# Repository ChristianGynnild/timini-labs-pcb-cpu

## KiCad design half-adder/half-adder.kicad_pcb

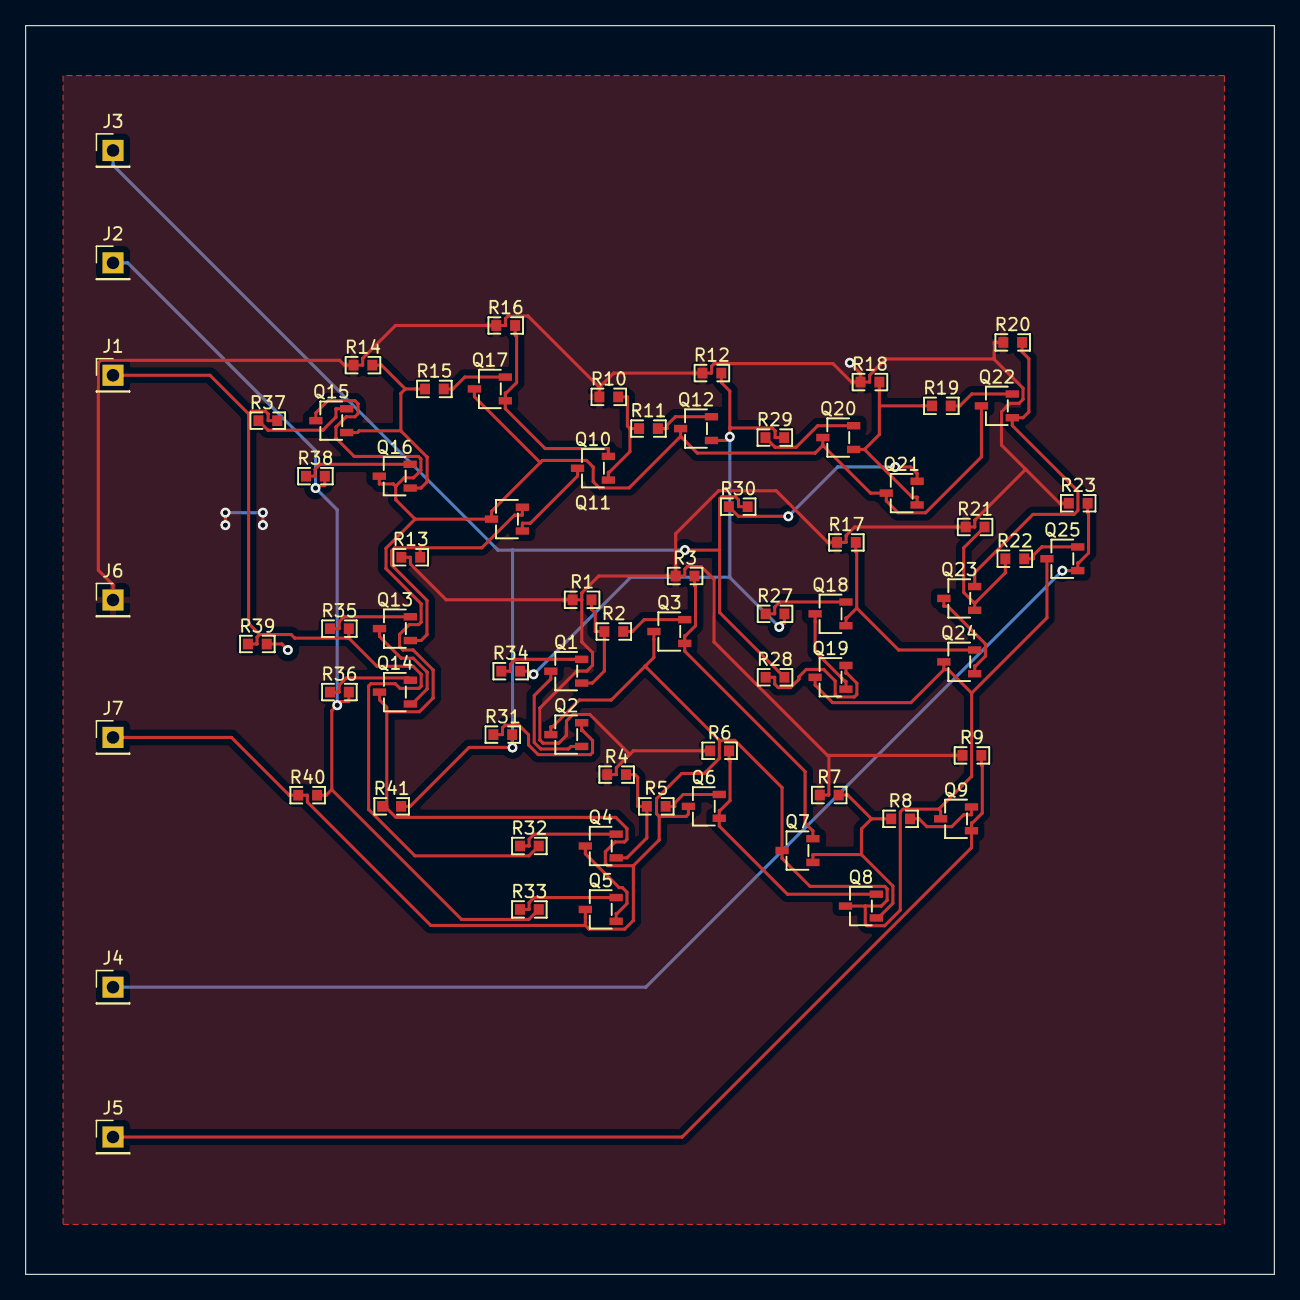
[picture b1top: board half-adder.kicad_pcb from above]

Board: 2 copper layers, 100.0 x 100.0 mm, 70 parts (0 on the bottom side), 46 nets.

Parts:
J1: A; PinHeader_1x01_P2.54mm_Vertical
J2: B; PinHeader_1x01_P2.54mm_Vertical
J3: C; PinHeader_1x01_P2.54mm_Vertical
J4: OUTPUT; PinHeader_1x01_P2.54mm_Vertical
J5: CARRY OUT; PinHeader_1x01_P2.54mm_Vertical
J6: 5V; PinHeader_1x01_P2.54mm_Vertical
J7: GROUND; PinHeader_1x01_P2.54mm_Vertical
Q1, Q2, Q3, Q4, Q5, Q6, Q7, Q8, Q9, Q10, Q11, Q12, Q13, Q14, Q15, Q16, Q17, Q18, Q19, Q20, Q21, Q22, Q23, Q24, Q25: NPN; SOT-23-3_L2.9-W1.6-P1.90-LS2.8-BR
R1, R3, R7, R8, R9, R10, R11, R12, R13, R14, R15, R16, R17, R18, R19, R20, R21, R22, R23: 3k; R0603
R2, R4, R5, R6: 1k; R0603
R27, R28, R29, R30, R31, R32, R33, R34, R35, R36, R37, R38: 10k; R0603
R39, R40, R41: 50k; R0603

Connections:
+5V: J6.1, R1.1, R3.1, R4.1, R6.1, R7.1, R9.1, R10.1, R12.1, R13.1, R14.1, R16.1, R17.1, R18.1, R20.1, R21.1, R23.1
/ORa: Q3.1 (C), Q7.2 (B), R3.2
/ORb: Q6.1 (C), Q8.2 (B), R6.2
GND: J7.1, Q2.3 (E), Q3.3 (E), Q5.3 (E), Q6.3 (E), Q7.3 (E), Q8.3 (E), Q9.3 (E), Q11.3 (E), Q12.3 (E), Q14.3 (E), Q15.3 (E), Q16.3 (E), Q17.3 (E), Q19.3 (E), Q20.3 (E), Q21.3 (E), Q22.3 (E), Q24.3 (E), Q25.3 (E), R39.2, R40.1, R41.1
unnamed: J1.1, R32.2, R35.2, R37.2, R39.1
unnamed: J2.1, R33.2, R36.2, R38.2, R40.2
unnamed: J3.1, R28.2, R30.2, R31.2, R41.2
unnamed: J4.1, Q25.1 (C), R23.2
unnamed: J5.1, Q9.1 (C), R9.2
unnamed: Q1.2 (B), R34.1
unnamed: Q1.1 (C), R1.2, R2.1
unnamed: Q1.3 (E), Q2.1 (C)
unnamed: Q2.2 (B), R31.1
unnamed: Q3.2 (B), R2.2
unnamed: Q4.2 (B), R32.1
unnamed: Q4.1 (C), R4.2, R5.1
unnamed: Q4.3 (E), Q5.1 (C)
unnamed: Q5.2 (B), R33.1
unnamed: Q6.2 (B), R5.2
unnamed: Q7.1 (C), Q8.1 (C), R7.2, R8.1
unnamed: Q9.2 (B), R8.2
unnamed: Q10.2 (B), Q17.1 (C), R16.2
unnamed: Q10.1 (C), R10.2, R11.1
unnamed: Q10.3 (E), Q11.1 (C)
unnamed: Q11.2 (B), Q13.1 (C), R13.2
unnamed: Q12.2 (B), R11.2
unnamed: Q12.1 (C), R12.2, R27.2, R29.2, R34.2
unnamed: Q13.2 (B), R35.1
unnamed: Q13.3 (E), Q14.1 (C)
unnamed: Q14.2 (B), R36.1
unnamed: Q15.2 (B), R37.1
unnamed: Q15.1 (C), Q16.1 (C), R14.2, R15.1
unnamed: Q16.2 (B), R38.1
unnamed: Q17.2 (B), R15.2
unnamed: Q18.2 (B), R27.1
unnamed: Q18.1 (C), Q24.2 (B), R17.2
unnamed: Q18.3 (E), Q19.1 (C)
unnamed: Q19.2 (B), R28.1
unnamed: Q20.2 (B), R29.1
unnamed: Q20.1 (C), Q21.1 (C), R18.2, R19.1
unnamed: Q21.2 (B), R30.1
unnamed: Q22.2 (B), R19.2
unnamed: Q22.1 (C), Q23.2 (B), R20.2
unnamed: Q23.1 (C), R21.2, R22.1
unnamed: Q23.3 (E), Q24.1 (C)
unnamed: Q25.2 (B), R22.2

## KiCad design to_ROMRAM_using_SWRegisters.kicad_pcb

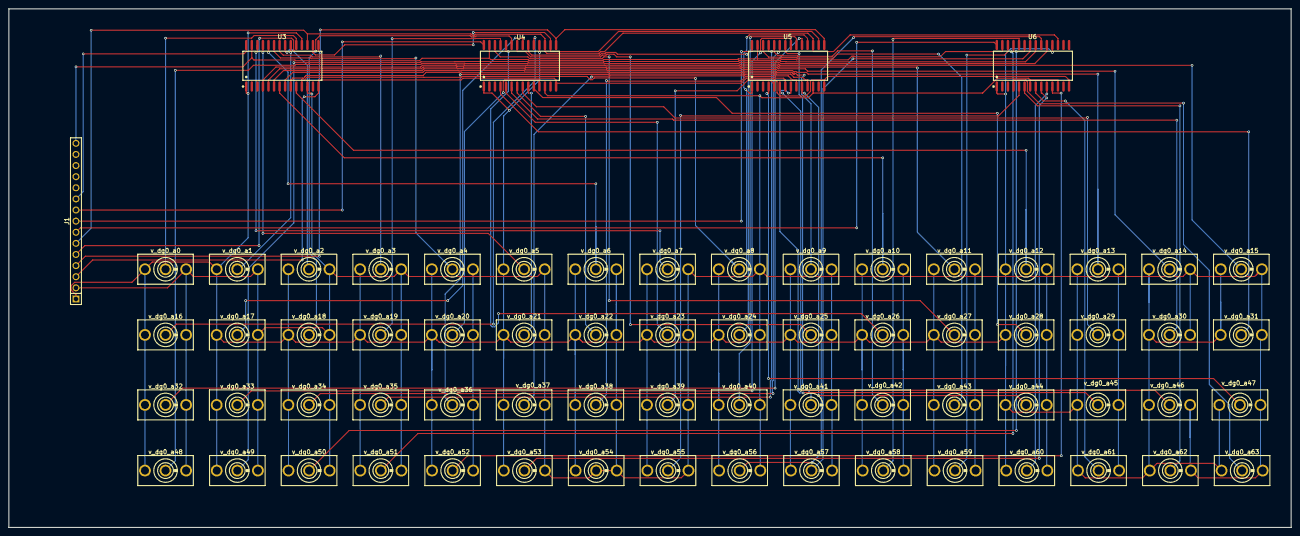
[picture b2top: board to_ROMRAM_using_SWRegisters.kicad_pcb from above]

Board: 2 copper layers, 293.0 x 118.5 mm, 69 parts (0 on the bottom side), 75 nets.

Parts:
J1: Conn_01x15; HDR-TH_15P-P2.54-V-M
U3, U4, U5, U6: HI9P0506-5; SOIC-28_L17.9-W7.5-P1.27-LS10.3-BL
v_dg0_a0, v_dg0_a1, v_dg0_a2, v_dg0_a3, v_dg0_a4, v_dg0_a5, v_dg0_a6, v_dg0_a7, v_dg0_a8, v_dg0_a9, v_dg0_a10, v_dg0_a11, v_dg0_a12, v_dg0_a13, v_dg0_a14, v_dg0_a15, v_dg0_a16, v_dg0_a17, v_dg0_a18, v_dg0_a19, v_dg0_a20, v_dg0_a21, v_dg0_a22, v_dg0_a23, v_dg0_a24, v_dg0_a25, v_dg0_a26, v_dg0_a27, v_dg0_a28, v_dg0_a29, v_dg0_a30, v_dg0_a31, v_dg0_a32, v_dg0_a33, v_dg0_a34, v_dg0_a35, v_dg0_a36, v_dg0_a37, v_dg0_a38, v_dg0_a39, v_dg0_a40, v_dg0_a41, v_dg0_a42, v_dg0_a43, v_dg0_a44, v_dg0_a45, v_dg0_a46, v_dg0_a47, v_dg0_a48, v_dg0_a49, v_dg0_a50, v_dg0_a51, v_dg0_a52, v_dg0_a53, v_dg0_a54, v_dg0_a55, v_dg0_a56, v_dg0_a57, v_dg0_a58, v_dg0_a59, v_dg0_a60, v_dg0_a61, v_dg0_a62, v_dg0_a63: SW_SPDT; SW-TH_100SP1T1B1M2QEH

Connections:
unnamed: J1.1, U3.1 (+VSUPPLY), U3.18 (ENABLE), U4.1 (+VSUPPLY), U4.18 (ENABLE), U5.1 (+VSUPPLY), U5.18 (ENABLE), U6.1 (+VSUPPLY), U6.18 (ENABLE), v_dg0_a0.1 (A), v_dg0_a1.1 (A), v_dg0_a2.1 (A), v_dg0_a3.1 (A), v_dg0_a4.1 (A), v_dg0_a5.1 (A), v_dg0_a6.1 (A), v_dg0_a7.1 (A), v_dg0_a8.1 (A), v_dg0_a9.1 (A), v_dg0_a10.1 (A), v_dg0_a11.1 (A), v_dg0_a12.1 (A), v_dg0_a13.1 (A), v_dg0_a14.1 (A), v_dg0_a15.1 (A), v_dg0_a16.1 (A), v_dg0_a17.1 (A), v_dg0_a18.1 (A), v_dg0_a19.1 (A), v_dg0_a20.1 (A), v_dg0_a21.1 (A), v_dg0_a22.1 (A), v_dg0_a23.1 (A), v_dg0_a24.1 (A), v_dg0_a25.1 (A), v_dg0_a26.1 (A), v_dg0_a27.1 (A), v_dg0_a28.1 (A), v_dg0_a29.1 (A), v_dg0_a30.1 (A), v_dg0_a31.1 (A), v_dg0_a32.1 (A), v_dg0_a33.1 (A), v_dg0_a34.1 (A), v_dg0_a35.1 (A), v_dg0_a36.1 (A), v_dg0_a37.1 (A), v_dg0_a38.1 (A), v_dg0_a39.1 (A), v_dg0_a40.1 (A), v_dg0_a41.1 (A), v_dg0_a42.1 (A), v_dg0_a43.1 (A), v_dg0_a44.1 (A), v_dg0_a45.1 (A), v_dg0_a46.1 (A), v_dg0_a47.1 (A), v_dg0_a48.1 (A), v_dg0_a49.1 (A), v_dg0_a50.1 (A), v_dg0_a51.1 (A), v_dg0_a52.1 (A), v_dg0_a53.1 (A), v_dg0_a54.1 (A), v_dg0_a55.1 (A), v_dg0_a56.1 (A), v_dg0_a57.1 (A), v_dg0_a58.1 (A), v_dg0_a59.1 (A), v_dg0_a60.1 (A), v_dg0_a61.1 (A), v_dg0_a62.1 (A), v_dg0_a63.1 (A)
unnamed: J1.2, U3.12 (GND), U4.12 (GND), U5.12 (GND), U6.12 (GND), v_dg0_a0.3 (C), v_dg0_a1.3 (C), v_dg0_a2.3 (C), v_dg0_a3.3 (C), v_dg0_a4.3 (C), v_dg0_a5.3 (C), v_dg0_a6.3 (C), v_dg0_a7.3 (C), v_dg0_a8.3 (C), v_dg0_a9.3 (C), v_dg0_a10.3 (C), v_dg0_a11.3 (C), v_dg0_a12.3 (C), v_dg0_a13.3 (C), v_dg0_a14.3 (C), v_dg0_a15.3 (C), v_dg0_a16.3 (C), v_dg0_a17.3 (C), v_dg0_a18.3 (C), v_dg0_a19.3 (C), v_dg0_a20.3 (C), v_dg0_a21.3 (C), v_dg0_a22.3 (C), v_dg0_a23.3 (C), v_dg0_a24.3 (C), v_dg0_a25.3 (C), v_dg0_a26.3 (C), v_dg0_a27.3 (C), v_dg0_a28.3 (C), v_dg0_a29.3 (C), v_dg0_a30.3 (C), v_dg0_a31.3 (C), v_dg0_a32.3 (C), v_dg0_a33.3 (C), v_dg0_a34.3 (C), v_dg0_a35.3 (C), v_dg0_a36.3 (C), v_dg0_a37.3 (C), v_dg0_a38.3 (C), v_dg0_a39.3 (C), v_dg0_a40.3 (C), v_dg0_a41.3 (C), v_dg0_a42.3 (C), v_dg0_a43.3 (C), v_dg0_a44.3 (C), v_dg0_a45.3 (C), v_dg0_a46.3 (C), v_dg0_a47.3 (C), v_dg0_a48.3 (C), v_dg0_a49.3 (C), v_dg0_a50.3 (C), v_dg0_a51.3 (C), v_dg0_a52.3 (C), v_dg0_a53.3 (C), v_dg0_a54.3 (C), v_dg0_a55.3 (C), v_dg0_a56.3 (C), v_dg0_a57.3 (C), v_dg0_a58.3 (C), v_dg0_a59.3 (C), v_dg0_a60.3 (C), v_dg0_a61.3 (C), v_dg0_a62.3 (C), v_dg0_a63.3 (C)
unnamed: J1.3, U3.14 (AdrA3), U4.14 (AdrA3), U5.14 (AdrA3), U6.14 (AdrA3)
unnamed: J1.4, U3.15 (AdrA2), U4.15 (AdrA2), U5.15 (AdrA2), U6.15 (AdrA2)
unnamed: J1.5, U3.16 (AdrA1), U4.16 (AdrA1), U5.16 (AdrA1), U6.16 (AdrA1)
unnamed: J1.6, U3.17 (AdrA0), U4.17 (AdrA0), U5.17 (AdrA0), U6.17 (AdrA0)
unnamed: J1.7, U6.28 (OUT)
unnamed: J1.8, U5.28 (OUT)
unnamed: J1.9, U4.28 (OUT)
unnamed: J1.10, U3.28 (OUT)
unnamed: J1.15, U3.27 (-VSUPPLY), U4.27 (-VSUPPLY), U5.27 (-VSUPPLY), U6.27 (-VSUPPLY)
unnamed: U3.19 (IN1), v_dg0_a0.2 (B)
unnamed: U3.20 (IN2), v_dg0_a1.2 (B)
unnamed: U3.21 (IN3), v_dg0_a2.2 (B)
unnamed: U3.22 (IN4), v_dg0_a3.2 (B)
unnamed: U3.23 (IN5), v_dg0_a4.2 (B)
unnamed: U3.24 (IN6), v_dg0_a6.2 (B)
unnamed: U3.25 (IN7), v_dg0_a5.2 (B)
unnamed: U3.26 (IN8), v_dg0_a7.2 (B)
unnamed: U3.11 (IN9), v_dg0_a8.2 (B)
unnamed: U3.10 (IN10), v_dg0_a12.2 (B)
unnamed: U3.9 (IN11), v_dg0_a9.2 (B)
unnamed: U3.8 (IN12), v_dg0_a13.2 (B)
unnamed: U3.7 (IN13), v_dg0_a10.2 (B)
unnamed: U3.6 (IN14), v_dg0_a14.2 (B)
unnamed: U3.5 (IN15), v_dg0_a11.2 (B)
unnamed: U3.4 (IN16), v_dg0_a15.2 (B)
unnamed: U4.19 (IN1), v_dg0_a16.2 (B)
unnamed: U4.20 (IN2), v_dg0_a24.2 (B)
unnamed: U4.21 (IN3), v_dg0_a17.2 (B)
unnamed: U4.22 (IN4), v_dg0_a25.2 (B)
unnamed: U4.23 (IN5), v_dg0_a18.2 (B)
unnamed: U4.24 (IN6), v_dg0_a26.2 (B)
unnamed: U4.25 (IN7), v_dg0_a19.2 (B)
unnamed: U4.26 (IN8), v_dg0_a27.2 (B)
unnamed: U4.11 (IN9), v_dg0_a20.2 (B)
unnamed: U4.10 (IN10), v_dg0_a28.2 (B)
unnamed: U4.9 (IN11), v_dg0_a21.2 (B)
unnamed: U4.8 (IN12), v_dg0_a29.2 (B)
unnamed: U4.7 (IN13), v_dg0_a22.2 (B)
unnamed: U4.6 (IN14), v_dg0_a30.2 (B)
unnamed: U4.5 (IN15), v_dg0_a23.2 (B)
unnamed: U4.4 (IN16), v_dg0_a31.2 (B)
unnamed: U5.19 (IN1), v_dg0_a32.2 (B)
unnamed: U5.20 (IN2), v_dg0_a40.2 (B)
unnamed: U5.21 (IN3), v_dg0_a33.2 (B)
unnamed: U5.22 (IN4), v_dg0_a41.2 (B)
unnamed: U5.23 (IN5), v_dg0_a34.2 (B)
unnamed: U5.24 (IN6), v_dg0_a42.2 (B)
unnamed: U5.25 (IN7), v_dg0_a35.2 (B)
unnamed: U5.26 (IN8), v_dg0_a43.2 (B)
unnamed: U5.11 (IN9), v_dg0_a36.2 (B)
unnamed: U5.10 (IN10), v_dg0_a44.2 (B)
unnamed: U5.9 (IN11), v_dg0_a37.2 (B)
unnamed: U5.8 (IN12), v_dg0_a45.2 (B)
unnamed: U5.7 (IN13), v_dg0_a38.2 (B)
unnamed: U5.6 (IN14), v_dg0_a46.2 (B)
unnamed: U5.5 (IN15), v_dg0_a39.2 (B)
unnamed: U5.4 (IN16), v_dg0_a47.2 (B)
unnamed: U6.19 (IN1), v_dg0_a48.2 (B)
unnamed: U6.20 (IN2), v_dg0_a56.2 (B)
unnamed: U6.21 (IN3), v_dg0_a49.2 (B)
unnamed: U6.22 (IN4), v_dg0_a57.2 (B)
unnamed: U6.23 (IN5), v_dg0_a50.2 (B)
unnamed: U6.24 (IN6), v_dg0_a58.2 (B)
unnamed: U6.25 (IN7), v_dg0_a51.2 (B)
unnamed: U6.26 (IN8), v_dg0_a59.2 (B)
unnamed: U6.11 (IN9), v_dg0_a52.2 (B)
unnamed: U6.10 (IN10), v_dg0_a60.2 (B)
unnamed: U6.9 (IN11), v_dg0_a53.2 (B)
unnamed: U6.8 (IN12), v_dg0_a61.2 (B)
unnamed: U6.7 (IN13), v_dg0_a54.2 (B)
unnamed: U6.6 (IN14), v_dg0_a62.2 (B)
unnamed: U6.5 (IN15), v_dg0_a55.2 (B)
unnamed: U6.4 (IN16), v_dg0_a63.2 (B)

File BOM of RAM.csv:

Reference,Value,Datasheet,Footprint,Qty,MPN,Part page
J1,Conn_01x15,~,1x15_conn:HDR-TH_15P-P2.54-V-M,1,Pin header1x15P 2.54mm,https://jlcpcb.com/partdetail/Made_InChina-1x15P_254mm/C54102 
"U3,U4,U5,U6",HI9P0506-5,https://jlcpcb.com/api/file/downloadByFileSystemAccessId/859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 ,16bitReg:SOIC-28_L17.9-W7.5-P1.27-LS10.3-BL,4,HI9P0506-5,https://jlcpcb.com/partdetail/TexasInstruments-HI9P05065/C3657429 
"v_dg0_a0,v_dg0_a1,v_dg0_a2,v_dg0_a3,v_dg0_a4,v_dg0_a5,v_dg0_a6,v_dg0_a7,v_dg0_a8,v_dg0_a9,v_dg0_a10,v_dg0_a11,v_dg0_a12,v_dg0_a13,v_dg0_a14,v_dg0_a15,v_dg0_a16,v_dg0_a17,v_dg0_a18,v_dg0_a19,v_dg0_a20,v_dg0_a21,v_dg0_a22,v_dg0_a23,v_dg0_a24,v_dg0_a25,v_dg0_a26,v_dg0_a27,v_dg0_a28,v_dg0_a29,v_dg0_a30,v_dg0_a31,v_dg0_a32,v_dg0_a33,v_dg0_a34,v_dg0_a35,v_dg0_a36,v_dg0_a37,v_dg0_a38,v_dg0_a39,v_dg0_a40,v_dg0_a41,v_dg0_a42,v_dg0_a43,v_dg0_a44,v_dg0_a45,v_dg0_a46,v_dg0_a47,v_dg0_a48,v_dg0_a49,v_dg0_a50,v_dg0_a51,v_dg0_a52,v_dg0_a53,v_dg0_a54,v_dg0_a55,v_dg0_a56,v_dg0_a57,v_dg0_a58,v_dg0_a59,v_dg0_a60,v_dg0_a61,v_dg0_a62,v_dg0_a63",SW_SPDT,https://jlcpcb.com/api/file/downloadByFileSystemAccessId/858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,SPDT:SW-TH_100SP1T1B1M2QEH,64,100SP1T1B1M2QEH,https://jlcpcb.com/partdetail/eswitch-100SP1T1B1M2QEH/C273351

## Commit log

2024-07-21 Schematic of half adder
2024-07-21 Fix gitignore .lck typo
2024-07-21 Create PCB layout
2024-07-21 Create schematic without hierarchical schematics
2024-07-21 Fix design rule checker errors
2024-07-22 Change resistors to more common type
2024-07-22 Gitignore .debug files
2024-10-28 Ngspice simulation
2024-12-22 Add ground plane to half adder and modularize or gate
2024-12-29 Use reusable or gate in half adder
2024-12-29 Improved logic gates
2024-12-29 replaced circuitry in half adder with reusable gates
2024-12-29 Clock project
2024-12-29 Add and gate to schematic
2024-12-29 Fixed gates and moved half adder to its own directory
2024-12-29 Remove unneeded or gate
2024-12-29 Remove capacitor connected to 5V and gnd
2024-12-30 Schematic for register
2024-12-31 Schematic of control-unit
2025-01-04 Footprints for resistor (R0603) and a transistor
2025-01-04 Assign footprints in half adder
2025-01-04 Alternative and gates with different amounts of inputs
2025-01-04 complete 2-bit encoder
2025-01-04 Rising edge diagram
2025-01-14 Global labels to local labels in control-unit
2025-01-14 Fix ADD command logic for control-unit
2025-01-14 Implement logic for jump instruction
2025-01-14 Optimize store and jump instruction circuit
2025-01-14 Moved wires to more easily do operating point analysis
2025-02-03 Xor, and & or gates footprint and symbol library
2025-02-03 Use IC circuits in adder circuit
2025-02-03 When i say BAM, i commit the beginning RAM (switch register hirearchy, no multiplexer)
2025-02-24 Sent ALU schematic, has at least one ERC error
2025-02-24 Added ALU schematic, contains some ERC errors.
2025-02-24 Revert " Added ALU schematic, contains some ERC errors."
    This reverts commit eea72f013f2a7a55b5a99c0928ed454a495ebb9c.
2025-02-24 Added ALU schematic, has some ERC errors
2025-02-24 A poem about importance
2025-03-18 ACtuall PCB, grb, drl and BOM of RAM
2025-03-18 own branch with all RAMs
